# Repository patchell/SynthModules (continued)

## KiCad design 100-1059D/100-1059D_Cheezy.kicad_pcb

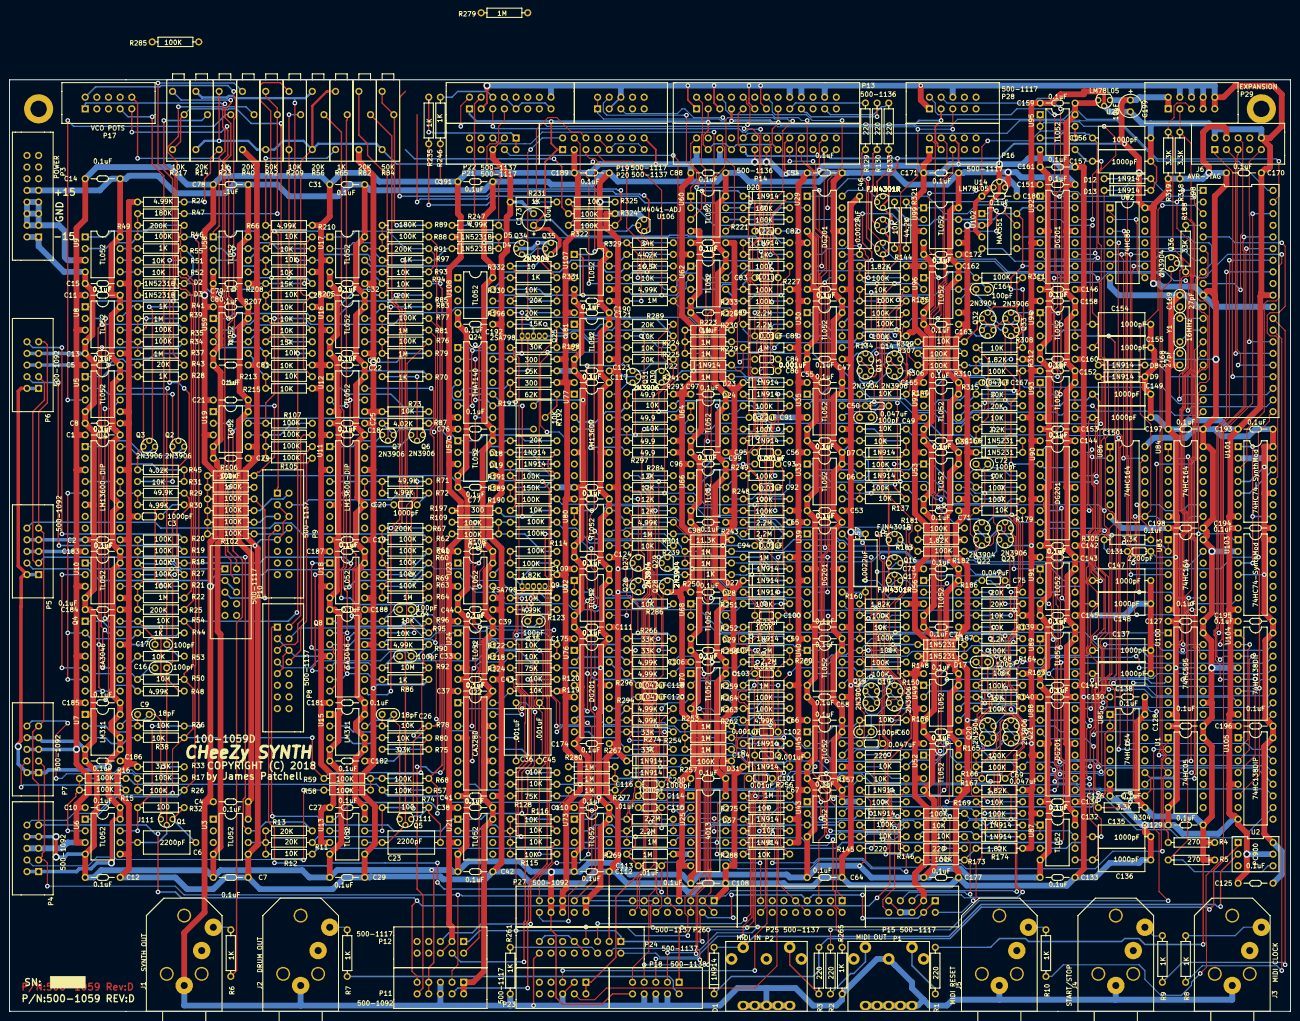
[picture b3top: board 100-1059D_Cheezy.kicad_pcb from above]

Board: 2 copper layers, 279.4 x 203.2 mm, 720 parts (0 on the bottom side), 505 nets.

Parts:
C1, C2, C4, C5, C7, C8, C10, C11, C12, C13, C14, C15, C18, C19, C21, C22, C24, C25, C27, C28, C29, C30, C31, C32, C37, C38, C39, C40, C41, C42, C43, C44, C47, C48, C51, C52, C53, C54, C55, C56, C58, C59, C62, C63, C64, C65, C66, C67, C70, C71, C73, C74, C76, C77, C87, C88, C89, C90, C96, C97, C98, C99, C105, C106, C107, C108, C109, C110, C111, C112, C117, C119, C121, C122, C123, C124, C125, C126, C127, C128, C129, C130, C132, C133, C134, C139, C140, C141, C142, C143, C144, C145, C146, C151, C152, C153, C158, C159, C160, C161, C162, C163, C165, C166, C170, C171, C172, C174, C175, C176, C177, C178, C179, C180, C181, C182, C183, C184, C185, C186, C187, C188, C189, C190, C191, C192, C193, C194, C195, C196, C197, C198, C200: 0.1uF; CAP-Bypass-0_3
C3, C20, C114, C116: 1000pF; CAP-GREENIE-0_2
C6, C23: 2200pF; CAP-AXIAL-0.5x0.2
C9, C26: 18pF; CAP-0.1
C16, C17, C33, C34, C35, C49, C60, C68, C72, C164: 100pF; CAP-0.1
C36, C45: .001uF; CAP-AXIAL-0.5x0.2
C46, C57: 0.0022uF; CAP-AXIAL-0.5x0.2
C50, C61, C69, C75, C118, C120, C167: 0.047uF; CAP-GREENIE-0_2
C78, C79, C80, C81: .1uF; CAP-Bypass-0_3
C82, C91, C100: 0.22uF; CAP-GREENIE-0_2
C83, C85, C92, C94, C101, C103: 0.01uF; CAP-GREENIE-0_2
C84, C86, C93, C95, C102, C104: 0.001uF; CAP-GREENIE-0_2
C113, C115: .01uF; CAP-GREENIE-0_2
C131: 2200pF; CAP-GREENIE-0_2
C135, C136, C137, C138, C147, C148, C149, C150, C154, C155, C156, C157: 1000pF; CAP-AXIAL-0.5x0.2
C168, C169: 27pF; CAP-0.1
C173, C199: 10uF; CapPol-Rad-0.2x0.1
D1, D6, D7, D8, D9, D10, D11, D12, D13, D14, D15, D18, D19, D20, D21, D22, D23, D24, D25, D26, D27, D28, D29, D30, D31, D32, D33, D35, D37: 1N914; DIODE0.4
D2, D3, D4, D5: 1N5231B; DIODE0.4
D16, D17, D38, D39: 1N5231; DIODE0.4
J1: SYNTH OUT; PHONE-SC112A
J2: DRUM OUT; PHONE-SC112A
J3: MIDI CLOCK; PHONE-SC112A
J4: START/STOP; PHONE-SC112A
J5: MIDI RESET; PHONE-SC112A
J6: AVR-JTAG; IDC5x2_Vert
P1: MIDI OUT; DIN-5-PIN
P2: MIDI IN; DIN-5-PIN
P3: POWER; IDC8x2_Vert
P4, P5, P6, P7, P11, P27: 500-1092; IDC5x2_Vert
P8, P9, P20, P22, P24, P25, P26: 500-1137; IDC8x2_Vert
P10, P12, P15, P16, P19, P21, P23, P28: 500-1117; IDC5x2_Vert
P13, P14: 500-1136; IDC13x2_Vert
P17: VCO POTS; IDC5x2_Vert
P18: 500-1138; IDC5x2_Vert
P29: EXPANSION; IDC5x2_Vert
P30, P31: PAD; MountingHole_140
Q1, Q5: J111; TO92
Q2, Q3, Q6, Q7, Q30, Q31: 2N3906; TO92
Q4, Q8: CA3046; DIP-14
Q9, Q25: 2SA798
Q10, Q11, Q12, Q15, Q16, Q17: FJN4301R; TO92
Q13, Q18, Q20, Q22, Q32: 2N3904; DUAL_TO92
Q14, Q19, Q21, Q23, Q33: 2N3906; DUAL_TO92
Q24: THAT140; DIP-14
Q26, Q27, Q28, Q29, Q34, Q35, Q36: 2N3904; TO92
R1, R2, R3, R129, R130, R133, R145, R146, R149: 220; AXIAL0_4
R4, R5: 270; AXIAL0_4
R6, R7, R8, R9, R10, R28, R41, R44, R55, R70, R83, R86, R97, R220, R231, R235, R246, R250, R261, R265, R331: 1K; AXIAL0_4
R11, R13, R43, R85, R184, R186, R196, R202, R289, R291, R313, R315, R333: 20K; AXIAL0_4
R12, R31, R36, R38, R51, R52, R53, R54, R73, R78, R80, R93, R94, R95, R96, R112, R113, R115, R116, R118, R119, R120, R122, R126, R127, R137, R139, R140, R141, R143, R153, R155, R156, R157, R159, R168, R169, R171, R175, R176, R179, R180, R185, R195, R203, R204, R205, R206, R207, R210, R211, R212, R213, R214, R215, R218, R219, R275, R286, R288, R290, R292, R299, R300, R302, R308, R309, R314, R320, R325, R327, R330: 10K; AXIAL0_4
R14, R40, R56, R82: 20K; Trimpot-3006
R15, R16, R17, R18, R19, R20, R21, R26, R27, R34, R35, R46, R57, R58, R59, R60, R61, R62, R63, R68, R69, R76, R77, R88, R98, R99, R100, R101, R102, R103, R104, R105, R106, R107, R108, R109, R110, R111, R114, R117, R131, R132, R134, R135, R136, R138, R142, R147, R148, R150, R151, R152, R154, R158, R161, R162, R163, R164, R165, R166, R170, R172, R173, R177, R178, R181, R182, R190, R191, R221, R222, R227, R233, R234, R236, R237, R242, R248, R249, R251, R252, R257, R263, R264, R285, R306, R307, R310, R311, R322, R324: 100K; AXIAL0_4
R22, R37, R39, R64, R79, R81, R223, R224, R225, R226, R229, R238, R239, R240, R241, R244, R253, R254, R255, R256, R259, R269, R273, R276, R277, R279, R280: 1M; AXIAL0_4
R23, R65: 1K; Trimpot-3006
R24, R30, R48, R66, R72, R90, R123, R232, R247, R262, R281, R282, R294, R296, R303: 4.99K; AXIAL0_4
R25, R49, R67, R91: 200K; AXIAL0_4
R29, R71: 49.9K; AXIAL0_4
R32, R74: 100; AXIAL0_4
R33, R75, R304, R305, R318, R319: 3.3K; AXIAL0_4
R42, R84: 50K; Trimpot-3006
R45, R87: 4.02K; AXIAL0_4
R47, R89: 180K; AXIAL0_4
R50, R92, R125: 10M; AXIAL0_4
R121, R144, R160, R167, R174, R183, R312: 1.82K; AXIAL0_4
R124, R128: 75K; AXIAL0_4
R187, R316: 2.2K; AXIAL0_4
R188, R266, R267, R274, R278: 33K; AXIAL0_4
R189: 150K; AXIAL0_4
R192: 10K; Trimpot
R193: 62K; AXIAL0_4
R194, R197, R201: 300; AXIAL0_4
R198: 30K; AXIAL0_4
R199, R200, R208, R216: 15K; AXIAL0_4
R209, R217: 10K; Trimpot-3006
R228, R230, R243, R245, R258, R260, R268, R272: 2.2M; AXIAL0_4
R270, R271, R283, R284: 12K; AXIAL0_4
R293, R295, R297, R298: 49.9; AXIAL0_4
R301: 11.3K; AXIAL0_4
R321, R328: 44.2K; AXIAL0_4
R326: 16.5K; AXIAL0_4
R329: 34K; AXIAL0_4
R332: 10; AXIAL0_4
U1: 74HC05; DIP-14
U2: PC900; DIP-6
U3, U5, U6, U8, U9, U10, U12, U13, U16, U17, U18, U19, U21, U23, U24, U30, U33, U35, U40, U43, U45, U49, U52, U53, U56, U57, U58, U59, U60, U62, U64, U66, U68, U70, U72, U73, U80, U81, U87, U89, U91, U93, U94, U95, U96, U97, U99, U107, U108: TL052; DIP8
U4, U11: LM13600-DIP; DIP-16
U7, U15: LM311; DIP8
U14, U20: LM78L05; TO92
U22: CA3280; DIP-16
U25: 4013; DIP-14
U29, U39, U76, U88, U90, U92: DG201; DIP-16
U77: LM13600; DIP-16
U82: 74HC86; DIP-14
U83, U84, U85, U86: 74HC164; DIP-14
U98: ATMEGA1284-dip; DIP-40
U100: 74HC595; DIP-16
U101, U103: 74HC74-SynthMod; DIP-14
U102: MAX551; DIP8
U104, U105: 74HC138DIP; DIP-16
U106: LM4041-ADJ; TO92
Y1: 16MHz; XTAL

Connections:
+10: C173.1, P12.1, P13.3, P13.7, P13.15, P14.3, P14.7, P14.15, P15.1, P15.4, P16.3, P20.1, P22.1, P24.1, P25.4, P25.7, P26.4, P28.3, Q35.1, R332.1, R333.2
+15V0: C1.1, C4.1, C5.1, C10.1, C11.1, C14.1, C18.1, C21.1, C22.1, C27.1, C28.1, C31.1, C37.1, C38.1, C39.1, C40.1, C48.1, C54.1, C55.1, C56.1, C59.1, C65.1, C66.1, C67.1, C70.1, C73.1, C76.1, C78.1, C80.1, C87.1, C88.1, C96.1, C97.1, C105.1, C106.1, C109.1, C110.1, C117.1, C121.1, C122.1, C132.1, C139.1, C140.1, C143.1, C144.1, C151.1, C152.1, C158.1, C159.1, C162.1, C165.1, C171.1, C175.1, C176.1, C178.1, C181.1, C183.1, C185.1, C187.1, C189.1, C191.1, C200.1, P3.9, P3.10, P4.1, P4.2, P5.1, P5.2, P6.1, P6.2, P7.1, P7.2, P11.1, P11.2, P18.1, P25.15, P26.11, P26.13, P26.15, P27.1, P27.2, Q34.3, R124.2, R128.2, R136.1, R141.1, R152.1, R157.1, R192.1, R198.1, R200.1, R203.1, R303.1, R325.1, U3.8, U4.11, U5.8, U6.8, U7.5, U7.6, U7.8, U8.8, U9.8, U10.8, U11.11, U12.8, U13.8, U14.3, U15.5, U15.6, U15.8, U16.8, U17.8, U18.8, U19.8, U20.3, U21.8, U22.11, U22.14, U23.8, U24.8, U25.5, U25.9, U25.14, U29.13, U30.8, U33.8, U35.8, U39.13, U40.8, U43.8, U45.8, U49.8, U52.8, U53.8, U56.8, U57.8, U58.8, U59.8, U60.8, U62.8, U64.8, U66.8, U68.8, U70.8, U72.8, U73.8, U76.13, U77.11, U80.8, U81.8, U87.8, U88.13, U89.8, U90.13, U91.8, U92.13, U93.8, U94.8, U95.8, U96.8, U97.8, U99.8, U107.8, U108.8
-10: R11.1, R125.1
-15V0: C2.1, C7.1, C8.1, C12.1, C13.1, C15.1, C19.1, C24.1, C25.1, C29.1, C30.1, C32.1, C41.1, C42.1, C43.1, C44.1, C47.1, C51.1, C52.1, C53.1, C58.1, C62.1, C63.1, C64.1, C71.1, C74.1, C77.1, C79.1, C81.1, C89.1, C90.1, C98.1, C99.1, C107.1, C108.1, C111.1, C112.1, C119.1, C123.1, C124.1, C133.1, C134.1, C141.1, C142.1, C145.1, C146.1, C153.1, C160.1, C161.1, C163.1, C166.1, C172.1, C174.1, C177.1, C179.1, C182.1, C184.1, C186.1, C188.1, C190.1, C192.1, P3.1, P3.2, P4.7, P4.8, P5.7, P5.8, P6.7, P6.8, P7.7, P7.8, P11.7, P11.8, P18.10, P27.7, P27.8, R138.2, R154.2, R189.2, R192.3, R199.2, U3.4, U4.6, U5.4, U6.4, U7.1, U7.4, U8.4, U9.4, U10.4, U11.6, U12.4, U13.4, U15.1, U15.4, U16.4, U17.4, U18.4, U19.4, U21.4, U22.4, U23.4, U24.4, U29.4, U30.4, U33.4, U35.4, U39.4, U40.4, U43.4, U45.4, U49.4, U52.4, U53.4, U56.4, U57.4, U58.4, U59.4, U60.4, U62.4, U64.4, U66.4, U68.4, U70.4, U72.4, U73.4, U76.4, U77.6, U80.4, U81.4, U87.4, U88.4, U89.4, U90.4, U91.4, U92.4, U93.4, U94.4, U95.4, U96.4, U97.4, U99.4, U107.4, U108.4
/+5Vref: P4.10, R14.1, R38.2, R50.1, R54.1, R56.1, R59.1, R80.2, R92.1, R96.1, R204.1, R212.1, R328.1, U107.7
/-5Vref: R14.3, R23.1, R42.3, R56.3, R65.1, R84.3, R205.1, R213.1, R327.2, R329.1, R330.1, U107.1
/CYMBAL: P25.5, R276.1, R280.1, U93.6, U93.7
/CYMBAL_LFO: P28.4, R306.2, U94.1, U94.2
/CYMBAL_TRG: R188.1, U98.4
/DRM1: R224.2, U91.1, U91.2
/DRM1_TRG: C83.1, D20.2, U98.19
/DRM2: R239.2, U91.6, U91.7
/DRM2_TRG: C92.1, D24.2, U98.20
/DRM3: R254.2, U93.1, U93.2
/DRM3_TRG: C101.1, D28.2, U98.21
/Drum Synth/CYMBAL/ATK2: P26.5, P26.6, R296.2
/Drum Synth/CYMBAL/ATTACK1: P25.8, P25.9, R282.2
/Drum Synth/CYMBAL/EG1: P27.3, R286.2, R291.1, U72.1, U72.2
/Drum Synth/CYMBAL/EG2: R289.1, R302.2, U80.1, U80.2
/Drum Synth/CYMBAL/LFO-A: P27.9, R299.2, U81.7
/Drum Synth/CYMBAL/OUT: P18.9, R300.2, U81.1
/Drum Synth/CYMBAL/REL1: P26.2, P26.3, R281.2
/Drum Synth/CYMBAL/REL2: P26.8, P26.9, R294.2
/Drum Synth/CYMBAL/RESONANCE: P25.2, R273.1
/Drum Synth/CYMBAL/SA0: R267.1, U25.13, U76.8
/Drum Synth/CYMBAL/SA1: R266.1, U25.12, U76.1
/Drum Synth/CYMBAL/SB0: R278.1, U25.1, U76.16
/Drum Synth/CYMBAL/SB1: R274.1, U25.2, U76.9
/Drum Synth/CYMBAL/TRIG: Q36.3, R203.2, U25.3, U25.11
/Drum Synth/DRUM1/OUT: P18.3, R234.1, U62.7
/Drum Synth/Drum2/OUT: P18.5, R249.1, U66.7
/Drum Synth/Drum3/OUT: P18.7, R264.1, U70.7
/Drum Synth/LFO: D38.1, R290.1, R308.1, R316.1
/Drum Synth/OUT: P18.2, R7.1
/FILT_PITCH: R110.1, U89.1, U89.2
/GLD_RATE_DN: R173.2, U95.6, U95.7
/GLD_RATE_UP: R166.2, U95.1, U95.2
/Midi/CLR_IRQ: U98.18, U103.1
/Midi/DAC: U29.10, U39.10, U88.2, U88.7, U88.10, U88.15, U90.2, U90.7, U90.10, U90.15, U92.2, U92.7, U92.10, U92.15, U99.7, U102.8
/Midi/DACDONE_IRQ: U98.16, U103.6
/Midi/DACSEL0: U98.36, U104.1, U105.1
/Midi/DACSEL1: U98.35, U104.2, U105.2
/Midi/DACSEL2: U98.34, U104.3, U105.3
/Midi/DACSEL3: U98.33, U104.5, U105.4
/Midi/DAC_CLK: U98.5, U101.11
/Midi/EG1_STATE_A: Q10.3, U29.1, U100.15
/Midi/EG1_STATE_B: Q11.3, U29.8, U100.1
/Midi/EG1_STATE_C: Q12.3, U29.16, U100.2
/Midi/EG2_STATE_A: Q15.3, U39.1, U100.3
/Midi/EG2_STATE_B: Q16.3, U39.8, U100.4
/Midi/EG2_STATE_C: Q17.3, U39.16, U100.5
/Midi/LD_DAC: U98.7, U101.3, U102.4
/Midi/LD_OUTPORT: U98.1, U100.12
/Midi/MIDI_CLOCK: R8.1, U98.28
/Midi/MIDI_IN: R5.2, U2.4, U98.14
/Midi/MIDI_OUT: U1.3, U98.15
/Midi/MIDI_RESET: R10.1, U98.38
/Midi/MOSI: U98.6, U100.14, U102.5
/Midi/SCL: P29.3, R318.2, U98.22
/Midi/SDA: P29.5, R319.2, U98.23
/Midi/SPICLK: U98.8, U100.11, U102.6
/Midi/START_STOP: R9.1, U98.29
/Midi/STB0: U88.1, U104.15
/Midi/STB1: U88.8, U104.14
/Midi/STB2: U88.16, U104.13
/Midi/STB3: U88.9, U104.12
/Midi/STB4: U90.1, U104.11
/Midi/STB5: U90.8, U104.10
/Midi/STB6: U90.16, U104.9
/Midi/STB7: U90.9, U104.7
/Midi/STB8: U92.1, U105.15
/Midi/STB9: U92.8, U105.14
/Midi/STB10: U92.16, U105.13
/Midi/STB11: U92.9, U105.12
/Midi/TCK: J6.1, U98.24
/Midi/TDI: J6.9, U98.27
/Midi/TDO: J6.3, U98.26
/Midi/TMS: J6.5, U98.25
/NOISE: C113.1, C131.1, P9.7, R305.2
/NOISE_CLOCK: U83.8, U84.8, U85.8, U86.8, U98.2
/PITCH: R162.2, U87.1, U87.2
/PITCH_BEND: R12.1, U89.6, U89.7
/PULSEWIDTH: R16.1, R57.1, U94.6, U94.7
/References/DACREF: R320.1, R322.1, R325.2, R326.2, U106.2
/Synth/ADSR: C50.2, P4.3, P7.3, P11.3, P16.4, R131.1, R177.2, U35.7
/Synth/EG1_READY: D8.2, D9.1, R143.1, U98.17
/Synth/EG1_SUS_V: P13.10, U98.39
/Synth/EG2_READY: D12.2, D13.1, R159.1, U98.3
/Synth/EG2_SUS_V: P14.10, U98.40
/Synth/Envelope1/ATTACK: P13.2, U29.2
/Synth/Envelope1/DECAY: P13.6, U29.7
/Synth/Envelope1/RELEASE: P13.14, U29.15
/Synth/Envelope1/TIMECONST: R142.2, U29.3, U29.6, U29.14
/Synth/Envelope2/ATTACK: P14.2, U39.2
/Synth/Envelope2/DECAY: P14.6, U39.7
/Synth/Envelope2/RELEASE: P14.14, U39.15
/Synth/Envelope2/TIMECONST: R158.2, U39.3, U39.6, U39.14
/Synth/Filter/BP: C36.2, P8.4, P12.4, R127.1, U24.1
/Synth/Filter/FC1: P12.2, R109.1
/Synth/Filter/FC2: P11.4, R111.1
/Synth/Filter/FC3: P11.10, R108.1
/Synth/Filter/IN: R106.2, R112.1, U19.1
/Synth/Filter/Q: P12.5, R113.1
/Synth/GLIDE/OUT: C69.2, R18.1, R60.1, R161.2, U52.7
/Synth/GLIDE/RAMP_DOWN_POT: P15.2, R172.2
/Synth/GLIDE/RAMP_UP_POT: P15.5, R165.2
/Synth/LFO: D16.1, P4.9, P5.9, P6.9, P7.9, P11.9, R179.1, R187.1
/Synth/Mixer/FIN1: P8.1, R116.2, R120.1, U21.1
/Synth/Mixer/FIN3: C45.2, P8.7, R115.2, U24.7
/Synth/Mixer/FOUT: R107.2, R196.2, U19.7
/Synth/Mixer/IN1: P10.1, R49.2, R51.2, U9.1
/Synth/Mixer/IN2: D2.1, P10.4, R55.1
/Synth/Mixer/IN3: P9.1, R91.2, R93.2, U17.1
/Synth/Mixer/IN4: D4.1, P9.4, R97.1
/Synth/OUT: R6.1, R202.1, U57.1
/Synth/PITCH POTS/POT1: P17.7, R21.1
/Synth/PITCH POTS/POT2: P17.3, R285.1
/Synth/PITCH POTS/minus1: P17.10, R219.2, U59.7
/Synth/PITCH POTS/minus2: P17.2, R211.2, U58.7
/Synth/PITCH POTS/plus1: P17.9, R218.2, U59.1
/Synth/PITCH POTS/plus2: P17.1, R210.2, U58.1
/Synth/PITCHBEND: P5.3, P6.3, R13.2, U3.7
/Synth/STB0: U29.9, U105.11
/Synth/STB1: U39.9, U105.10
/Synth/VCA/CV: C61.2, R147.1, R190.2, U45.7
/Synth/VCO1/PWM1: P7.4, R15.1
/Synth/VCO1/PWM3: P7.10, R17.1
/Synth/VCO1/TRACKING: R25.2, R40.2
/Synth/VCO1/VCO2: P6.4, R19.1
/Synth/VCO1/VCO3: P6.10, R20.1
/Synth/VCO2/PWM2: P4.4, R58.1
/Synth/VCO2/TRACKING: R67.2, R82.2
/Synth/VCO2/VCO2: P5.4, R61.1
/Synth/VCO2/VCO3: P5.10, R62.1
/VCO2_OFFSET: R63.1, U87.6, U87.7
GND: C1.2, C2.2, C3.2, C4.2, C5.2, C7.2, C8.2, C10.2, C11.2, C12.2, C13.2, C14.2, C15.2, C18.2, C19.2, C20.2, C21.2, C22.2, C24.2, C25.2, C27.2, C28.2, C29.2, C30.2, C31.2, C32.2, C37.2, C38.2, C39.2, C40.2, C41.2, C42.2, C43.2, C44.2, C46.2, C47.2, C48.2, C51.2, C52.2, C53.2, C54.2, C55.2, C56.2, C57.2, C58.2, C59.2, C62.2, C63.2, C64.2, C65.2, C66.2, C67.2, C70.2, C71.2, C73.2, C74.2, C76.2, C77.2, C78.2, C79.2, C80.2, C81.2, C82.2, C85.2, C87.2, C88.2, C89.2, C90.2, C91.2, C94.2, C96.2, C97.2, C98.2, C99.2, C100.2, C103.2, C105.2, C106.2, C107.2, C108.2, C109.2, C110.2, C111.2, C112.2, C115.2, C117.2, C118.2, C119.2, C120.2, C121.2, C122.2, C123.2, C124.2, C125.2, C126.2, C127.2, C128.2, C129.2, C130.2, C131.2, C132.2, C133.2, C134.2, C135.2, C136.2, C137.2, C138.2, C139.2, C140.2, C141.2, C142.2, C143.2, C144.2, C145.2, C146.2, C147.2, C148.2, C149.2, C150.2, C151.2, C152.2, C153.2, C154.2, C155.2, C156.2, C157.2, C158.2, C159.2, C160.2, C161.2, C162.2, C163.2, C165.2, C166.2, C168.2, C169.2, C170.2, C171.2, C172.2, C173.2, C174.2, C175.2, C176.2, C177.2, C178.2, C179.2, C180.2, C181.2, C182.2, C183.2, C184.2, C185.2, C186.2, C187.2, C188.2, C189.2, C190.2, C191.2, C192.2, C193.2, C194.2, C195.2, C196.2, C197.2, C198.2, C199.2, C200.2, D3.1, D5.1, D9.2, D13.2, D17.1, D23.1, D27.1, D31.1, D33.1, D35.2, D37.2, D39.1, J1.1, J2.1, J3.1, J4.1, J5.1, J6.2, J6.10, P1.2, P1.6, P1.7, P1.8, P1.9, P1.10, P2.6, P2.7, P2.8, P2.9, P2.10, P3.3, P3.4, P3.5, P3.6, P3.7, P3.8, P4.5, P4.6, P5.5, P5.6, P6.5, P6.6, P7.5, P7.6, P8.3, P8.6, P8.9, P9.3, P9.6, P9.9, P10.3, P10.6, P11.5, P11.6, P12.3, P12.6, P13.1, P13.5, P13.11, P13.13, P13.18, P13.20, P13.24, P14.1, P14.5, P14.11, P14.13, P14.18, P14.20, P14.24, P15.3, P15.6, P15.8, P15.9, P16.1, P16.6, P18.4, P18.6, P18.8, P19.3, P19.6, P20.3, P20.16, P21.3, P21.6, P22.3, P22.16, P23.3, P23.6, P24.3, P24.16, P25.6, P26.1, P26.7, P27.5, P27.6, P28.1, P28.6, P29.4, P29.6, P29.7, P29.8, P29.9, P29.10, Q4.4, Q4.12, Q8.4, Q8.12, Q9.5, Q13.5, Q14.2, Q18.5, Q19.2, Q20.5, Q21.2, Q22.5, Q23.2, Q24.7, Q25.4, Q25.5, Q26.1, Q27.1, Q28.1, Q29.1, Q30.2, Q31.2, Q32.5, Q33.2, Q36.1, R24.2, R31.2, R33.2, R37.2, R40.3, R44.2, R45.2, R66.2, R73.2, R75.2, R79.2, R82.3, R86.2, R87.2, R119.1, R121.2, R126.1, R134.2, R144.2, R150.2, R160.2, R163.1, R167.2, R174.2, R183.2, R185.2, R194.2, R197.2, R201.2, R206.2, R207.2, R214.2, R215.2, R227.2, R229.2, R231.2, R242.2, R244.2, R246.2, R257.2, R259.2, R261.2, R265.2, R269.2, R293.2, R295.2, R297.2, R298.2, R301.2, R312.2, R314.2, R324.2, U1.7, U2.5, U3.5, U4.3, U4.14, U5.5, U6.3, U6.5, U8.3, U9.3, U10.3, U10.5, U11.3, U11.14, U12.5, U13.3, U13.5, U14.2, U16.3, U17.3, U18.3, U18.5, U19.3, U19.5, U20.2, U21.3, U23.3, U23.5, U24.3, U24.5, U25.6, U25.7, U25.8, U29.5, U35.3, U35.5, U39.5, U45.3, U45.5, U49.3, U52.3, U52.5, U53.5, U56.3, U57.3, U57.5, U62.5, U66.5, U70.5, U76.5, U81.3, U81.5, U82.7, U83.7, U84.7, U85.7, U86.7, U88.5, U90.5, U92.5, U96.5, U97.3, U98.11, U98.31, U99.3, U99.5, U100.8, U100.13, U101.7, U102.2, U103.7, U104.8, U105.5, U105.8, U106.3, U107.3, U107.5, U108.3, U108.5
unnamed: C3.1, R30.2
unnamed: C6.1, Q1.2, Q4.1, U6.6
unnamed: C6.2, Q1.1, R32.1
unnamed: C9.1, R36.2, U7.2
unnamed: C9.2, Q1.3, R33.1, U7.7
unnamed: C16.1, Q4.5, R50.2, U10.2
unnamed: C16.2, R48.2, U10.1
unnamed: C17.1, Q4.14, R54.2, U5.6
unnamed: C17.2, R53.2, U5.7
unnamed: C20.1, R72.2
unnamed: C23.1, Q5.2, Q8.1, U13.6
unnamed: C23.2, Q5.1, R74.1
unnamed: C26.1, R78.2, U15.2
unnamed: C26.2, Q5.3, R75.1, U15.7
unnamed: C33.1, Q8.5, R92.2, U18.2
unnamed: C33.2, R90.2, U18.1
unnamed: C34.1, Q8.14, R96.2, U12.6
unnamed: C34.2, R95.2, U12.7
unnamed: C35.1, Q9.4, R125.2, U23.2
unnamed: C35.2, R123.2, U23.1
unnamed: C36.1, U22.13, U24.2
unnamed: C45.1, U22.12, U24.6
unnamed: C46.1, U29.11, U30.5
unnamed: C49.1, R140.2, U35.1
unnamed: C49.2, Q13.3, Q14.3, R139.2, U35.2
unnamed: C50.1, Q13.6, Q14.6, U35.6
unnamed: C57.1, U39.11, U40.5
unnamed: C60.1, R156.2, U45.1
unnamed: C60.2, Q18.3, Q19.3, R155.2, U45.2
unnamed: C61.1, Q18.6, Q19.6, U45.6
unnamed: C68.1, R171.2, U49.1
unnamed: C68.2, Q20.3, Q21.3, R168.2, U49.2
unnamed: C69.1, Q20.6, Q21.6, U52.6
unnamed: C72.1, R180.2, U53.7
unnamed: C72.2, Q22.3, Q23.3, R179.2, U53.6
unnamed: C75.1, Q22.6, Q23.6, U56.2
unnamed: C75.2, R184.2, U56.1
unnamed: C82.1, D20.1, D21.2, U60.3
unnamed: C83.2, R227.1, U62.3
unnamed: C84.1, R226.1, R228.1, U62.2
unnamed: C84.2, C86.1, D22.2, R223.1, R224.1, R225.1, R229.1
unnamed: C85.1, R228.2, R230.1
unnamed: C86.2, P20.4, R230.2, R232.2, U62.1
unnamed: C91.1, D24.1, D25.2, U64.3
unnamed: C92.2, R242.1, U66.3
unnamed: C93.1, R241.1, R243.1, U66.2
unnamed: C93.2, C95.1, D26.2, R238.1, R239.1, R240.1, R244.1
unnamed: C94.1, R243.2, R245.1
unnamed: C95.2, P22.4, R245.2, R247.2, U66.1
unnamed: C100.1, D28.1, D29.2, U68.3
unnamed: C101.2, R257.1, U70.3
unnamed: C102.1, R256.1, R258.1, U70.2
unnamed: C102.2, C104.1, D30.2, R253.1, R254.1, R255.1, R259.1
unnamed: C103.1, R258.2, R260.1
unnamed: C104.2, P24.4, R260.2, R262.2, U70.1
unnamed: C113.2, R269.1, U73.3
unnamed: C114.1, R268.1, R273.2, U73.2
unnamed: C114.2, C116.1, D32.2, R276.2, R277.2, R279.2, R280.2
unnamed: C115.1, R268.2, R272.1
unnamed: C116.2, P25.1, R272.2, R292.1, U73.1
unnamed: C118.1, U72.3, U76.3, U76.6
unnamed: C120.1, U76.11, U76.14, U80.3
unnamed: C126.1, R304.2, U83.9, U84.9, U85.9, U86.9
unnamed: C135.1, U87.3, U88.3
unnamed: C136.1, U87.5, U88.6
unnamed: C137.1, U88.14, U89.3
unnamed: C138.1, U88.11, U89.5
unnamed: C147.1, U90.3, U91.3
unnamed: C148.1, U90.6, U91.5
unnamed: C149.1, U90.14, U93.3
unnamed: C150.1, U90.11, U93.5
unnamed: C154.1, U92.3, U94.3
unnamed: C155.1, U92.6, U94.5
unnamed: C156.1, U92.14, U95.3
unnamed: C157.1, U92.11, U95.5
unnamed: C164.1, R309.2, U96.7
unnamed: C164.2, Q32.3, Q33.3, R308.2, U96.6
unnamed: C167.1, Q32.6, Q33.6, U97.2
unnamed: C167.2, R313.2, U97.1
unnamed: C168.1, U98.13, Y1.1
unnamed: C169.1, U98.12, Y1.2
unnamed: C180.1, U14.1, U102.3
unnamed: D1.1, R3.2, U2.1
unnamed: D1.2, P2.5, U2.2
unnamed: D2.2, D3.2
unnamed: D4.2, D5.2
unnamed: D6.1, U33.1
unnamed: D6.2, D7.2, R141.2, R143.2
unnamed: D7.1, U33.7
unnamed: D10.1, U43.1
unnamed: D10.2, D11.2, R157.2, R159.2
unnamed: D11.1, U43.7
unnamed: D14.1, D15.2, R170.1, U52.1
unnamed: D14.2, R176.2
unnamed: D15.1, R175.2
unnamed: D16.2, D17.2
unnamed: D18.1, D19.2, U57.7
unnamed: D18.2, R189.1, R190.1, R191.2, U57.6
unnamed: D19.1, R191.1, R195.2
unnamed: D21.1, R220.1
unnamed: D22.1, D23.2
unnamed: D25.1, R235.1
unnamed: D26.1, D27.2
unnamed: D29.1, R250.1
unnamed: D30.1, D31.2
unnamed: D32.1, D33.2
unnamed: D35.1, R275.1, U25.10
unnamed: D37.1, R288.1, U25.4
unnamed: D38.2, D39.2
unnamed: J1.3, R6.2
unnamed: J2.3, R7.2
unnamed: J3.3, R8.2
unnamed: J4.3, R9.2
unnamed: J5.3, R10.2
unnamed: J6.6, U98.9
unnamed: P1.4, R1.1
unnamed: P1.5, R2.1
unnamed: P2.4, R3.1
unnamed: P8.2, R103.1
unnamed: P8.5, R104.1
unnamed: P8.8, R105.1
unnamed: P9.2, R100.1
unnamed: P9.5, R101.1
unnamed: P9.8, R102.1
unnamed: P10.2, R98.1
unnamed: P10.5, R99.1
unnamed: P13.17, R129.2
unnamed: P13.19, R130.2
unnamed: P13.23, R133.2
unnamed: P14.17, R145.2
unnamed: P14.19, R146.2
unnamed: P14.23, R149.2
unnamed: P15.7, R175.1
unnamed: P15.10, R176.1
unnamed: P16.2, R181.2
unnamed: P16.5, U53.3
unnamed: P19.1, P19.2, R220.2
unnamed: P19.4, R221.2, U60.1, U60.2
unnamed: P19.5, U60.5
unnamed: P20.2, R223.2
unnamed: P20.5, R226.2
unnamed: P20.6, R231.1
unnamed: P20.7, R232.1, R233.2
unnamed: P20.8, P20.9, P20.15
unnamed: P21.1, P21.2, R235.2
unnamed: P21.4, R236.2, U64.1, U64.2
unnamed: P21.5, U64.5
unnamed: P22.2, R238.2
unnamed: P22.5, R241.2
unnamed: P22.6, R246.1
unnamed: P22.7, R247.1, R248.2
unnamed: P22.8, P22.9, P22.15
unnamed: P23.1, P23.2, R250.2
unnamed: P23.4, R251.2, U68.1, U68.2
unnamed: P23.5, U68.5
unnamed: P24.2, R253.2
unnamed: P24.5, R256.2
unnamed: P24.6, R261.1
unnamed: P24.7, R262.1, R263.2
unnamed: P24.8, P24.9, P24.15
unnamed: P25.3, R265.1
unnamed: P25.16, R271.2
unnamed: P26.12, R270.2
unnamed: P26.14, R284.2
unnamed: P26.16, R283.2
unnamed: P27.4, R279.1
unnamed: P27.10, R277.1
unnamed: P28.2, R310.2
unnamed: P28.5, U96.3
unnamed: Q2.1, R31.1, U5.2
unnamed: Q2.2, R28.1
unnamed: Q2.3, U4.16
unnamed: Q3.1, R39.2, R45.1
unnamed: Q3.2, R41.1
unnamed: Q3.3, U4.1
unnamed: Q4.2, Q4.6, R44.1, U4.5
unnamed: Q4.3, Q4.7, R35.1, R48.1
unnamed: Q4.8, R43.2, U8.2
unnamed: Q4.10, Q4.13, R34.1, R53.1
unnamed: Q6.1, R73.1, U12.2
unnamed: Q6.2, R70.1
unnamed: Q6.3, U11.16
unnamed: Q7.1, R81.2, R87.1
unnamed: Q7.2, R83.1
unnamed: Q7.3, U11.1
unnamed: Q8.2, Q8.6, R86.1, U11.5
unnamed: Q8.3, Q8.7, R77.1, R90.1
unnamed: Q8.8, R85.2, U16.2
unnamed: Q8.10, Q8.13, R76.1, R95.1
unnamed: Q9.1, R117.2, R121.1
unnamed: Q9.2, R118.2, R122.2
unnamed: Q9.3, R123.1
unnamed: Q10.2, R129.1
unnamed: Q11.2, R130.1
unnamed: Q12.2, R133.1
unnamed: Q13.1, Q13.4, Q14.1, Q14.4, R140.1
unnamed: Q13.2, Q14.5, R142.1, R144.1
unnamed: Q15.2, R145.1
unnamed: Q16.2, R146.1
unnamed: Q17.2, R149.1
unnamed: Q18.1, Q18.4, Q19.1, Q19.4, R156.1
unnamed: Q18.2, Q19.5, R158.1, R160.1
unnamed: Q20.1, Q20.4, Q21.1, Q21.4, R171.1
unnamed: Q20.2, R165.1, R166.1, R167.1
unnamed: Q21.5, R172.1, R173.1, R174.1
unnamed: Q22.1, Q22.4, Q23.1, Q23.4, R180.1
unnamed: Q22.2, Q23.5, R181.1, R182.1, R183.1
unnamed: Q24.1, Q24.6, Q25.1, R196.1
unnamed: Q24.2, Q24.9, R195.1, R197.1
unnamed: Q24.5, R193.1, R194.1
unnamed: Q24.4, Q24.10, R198.2
unnamed: Q24.3, Q24.12, Q25.2, R199.1
unnamed: Q24.13, R201.1
unnamed: Q24.8, Q24.14, R202.2, U57.2
unnamed: Q25.3, R200.2
unnamed: Q26.2, R266.2
unnamed: Q26.3, R270.1
unnamed: Q27.2, R267.2
unnamed: Q27.3, R271.1
unnamed: Q28.2, R274.2
unnamed: Q28.3, R283.1
unnamed: Q29.2, R278.2
unnamed: Q29.3, R284.1
unnamed: Q30.1, R289.2
unnamed: Q31.1, R291.2
unnamed: Q31.3, U77.16
unnamed: Q32.1, Q32.4, Q33.1, Q33.4, R309.1
unnamed: Q32.2, Q33.5, R310.1, R311.1, R312.1
unnamed: Q34.1, Q35.2, R332.2
unnamed: Q34.2, Q35.3, R331.1
unnamed: Q36.2, R188.2
unnamed: R2.2, U1.2
unnamed: R4.2, U1.1, U1.4
unnamed: R11.2, R12.2, R13.1, U3.6
unnamed: R14.2, R22.1
unnamed: R15.2, R16.2, R17.2, R26.1, U6.2
unnamed: R18.2, R19.2, R20.2, R21.2, R22.2, R25.1, R27.1, U10.6
unnamed: R23.2, U5.3
unnamed: R23.3, R24.1
unnamed: R26.2, R52.2, U6.1
unnamed: R27.2, R29.1, U10.7
unnamed: R28.2, U5.1
unnamed: R29.2, R30.1, U4.4, U4.12, U4.13
unnamed: R32.2, R36.1, R46.1, U6.7
unnamed: R34.2, R37.1, U8.5
unnamed: R35.2, R39.1, U8.6
unnamed: R38.1, U7.3
unnamed: R40.1, R43.1, U8.1
unnamed: R41.2, U8.7
unnamed: R42.1, R42.2, R47.1
unnamed: R46.2, R47.2, R49.1, U9.2
unnamed: R51.1, U9.6
unnamed: R52.1, U9.5
unnamed: R55.2, U9.7
unnamed: R56.2, R64.1
unnamed: R57.2, R58.2, R59.2, R68.1, U13.2
unnamed: R65.2, U12.3
unnamed: R65.3, R66.1
unnamed: R68.2, R94.2, U13.1
unnamed: R69.2, R71.1, U18.7
unnamed: R70.2, U12.1
unnamed: R71.2, R72.1, U11.4, U11.12, U11.13
unnamed: R74.2, R78.1, R88.1, U13.7
unnamed: R76.2, R79.1, U16.5
unnamed: R77.2, R81.1, U16.6
unnamed: R80.1, U15.3
unnamed: R82.1, R85.1, U16.1
unnamed: R83.2, U16.7
unnamed: R84.1, R84.2, R89.1
unnamed: R88.2, R89.2, R91.1, U17.2
unnamed: R93.1, U17.6
unnamed: R94.1, U17.5
unnamed: R97.2, U17.7
unnamed: R98.2, R99.2, R100.2, R101.2, R102.2, R106.1, U19.2
unnamed: R103.2, R104.2, R105.2, R107.1, U19.6
unnamed: R108.2, R109.2, R110.2, R111.2, R114.1, U23.6
unnamed: R112.2, R113.2, R115.1, R116.1, U21.2
unnamed: R114.2, R117.1, U23.7
unnamed: R118.1, U22.3
unnamed: R119.2, U22.16
unnamed: R120.2, U22.15
unnamed: R122.1, U22.6
unnamed: R124.1, U22.1
unnamed: R126.2, U22.9
unnamed: R127.2, U22.10
unnamed: R128.1, U22.8
unnamed: R131.2, R135.1, U30.2
unnamed: R132.1, U30.6, U30.7
unnamed: R132.2, R134.1, U30.3
unnamed: R135.2, R139.1, U30.1, U33.3, U33.6
unnamed: R136.2, R137.1, U33.2
unnamed: R137.2, R138.1, U33.5
unnamed: R147.2, R151.1, U40.2
unnamed: R148.1, U40.6, U40.7
unnamed: R148.2, R150.1, U40.3
unnamed: R151.2, R155.1, U40.1, U43.3, U43.6
unnamed: R152.2, R153.1, U43.2
unnamed: R153.2, R154.1, U43.5
unnamed: R161.1, R164.2, U49.6
unnamed: R162.1, R163.2, U49.5
unnamed: R164.1, R168.1, R169.2, U49.7
unnamed: R169.1, R170.2, U52.2
unnamed: R177.1, R178.2, U53.2
unnamed: R178.1, R182.2, U53.1
unnamed: R184.1, U56.6
unnamed: R185.1, R186.2, U56.5
unnamed: R186.1, R187.2, U56.7
unnamed: R192.2, R193.2
unnamed: R204.2, R206.1, U58.3
unnamed: R205.2, R207.1, U58.5
unnamed: R208.1, R210.1, U58.2
unnamed: R208.2, R209.2, R209.3
unnamed: R209.1, R211.1, U58.6
unnamed: R212.2, R214.1, U59.3
unnamed: R213.2, R215.1, U59.5
unnamed: R216.1, R218.1, U59.2
unnamed: R216.2, R217.2, R217.3
unnamed: R217.1, R219.1, U59.6
unnamed: R221.1, R222.2, U60.6
unnamed: R222.1, R225.2, U60.7
unnamed: R233.1, R234.2, U62.6
unnamed: R236.1, R237.2, U64.6
unnamed: R237.1, R240.2, U64.7
unnamed: R248.1, R249.2, U66.6
unnamed: R251.1, R252.2, U68.6
unnamed: R252.1, R255.2, U68.7
unnamed: R263.1, R264.2, U70.6
unnamed: R275.2, U72.7
unnamed: R281.1, U76.2
unnamed: R282.1, U76.7
unnamed: R60.2, R61.2, R62.2, R63.2, R64.2, R67.1, R69.1, R285.2, U18.6
unnamed: R286.1, U72.5
unnamed: R288.2, U80.7
unnamed: R290.2, R293.1, U77.4
unnamed: R292.2, R295.1, U77.13
unnamed: R294.1, U76.10
unnamed: R296.1, U76.15
unnamed: R297.1, U77.3
unnamed: R298.1, U77.14
unnamed: R299.1, U77.5, U81.6
unnamed: R300.1, U77.12, U81.2
unnamed: R301.1, R303.2, U72.6, U80.6
unnamed: R302.1, U80.5
unnamed: R305.1, U82.5, U86.13
unnamed: R306.1, R307.2, U96.2
unnamed: R307.1, R311.2, U96.1
unnamed: R313.1, U97.6
unnamed: R314.1, R315.2, U97.5
unnamed: R315.1, R316.2, U97.7
unnamed: R320.2, R321.1, U99.2
unnamed: R321.2, U99.1, U102.7
unnamed: R326.1, R329.2, U107.2
unnamed: R327.1, R328.2, U107.6
unnamed: R330.2, R333.1, U108.6
unnamed: R331.2, U108.7
unnamed: U82.1, U82.6
unnamed: U82.2, U82.8
unnamed: U82.3, U83.1, U83.2
unnamed: U82.4, U85.11
unnamed: U82.9, U83.3
unnamed: U82.10, U83.4
unnamed: U83.13, U84.1, U84.2
unnamed: U84.13, U85.1, U85.2
unnamed: U85.13, U86.1, U86.2
unnamed: U101.1, U101.8, U103.3, U104.6, U105.6
unnamed: U101.5, U101.12
unnamed: U99.6, U102.1
unnamed: U108.1, U108.2
VCC: C125.1, C127.1, C128.1, C129.1, C130.1, C170.1, C193.1, C194.1, C195.1, C196.1, C197.1, C198.1, C199.1, D8.1, D12.1, J6.4, P13.9, P14.9, P29.1, P29.2, Q10.1, Q11.1, Q12.1, Q15.1, Q16.1, Q17.1, R1.2, R4.1, R5.1, R304.1, R318.1, R319.1, U1.14, U2.6, U20.1, U82.14, U83.14, U84.14, U85.14, U86.14, U98.10, U98.30, U100.10, U100.16, U101.2, U101.4, U101.10, U101.13, U101.14, U103.2, U103.4, U103.14, U104.4, U104.16, U105.16

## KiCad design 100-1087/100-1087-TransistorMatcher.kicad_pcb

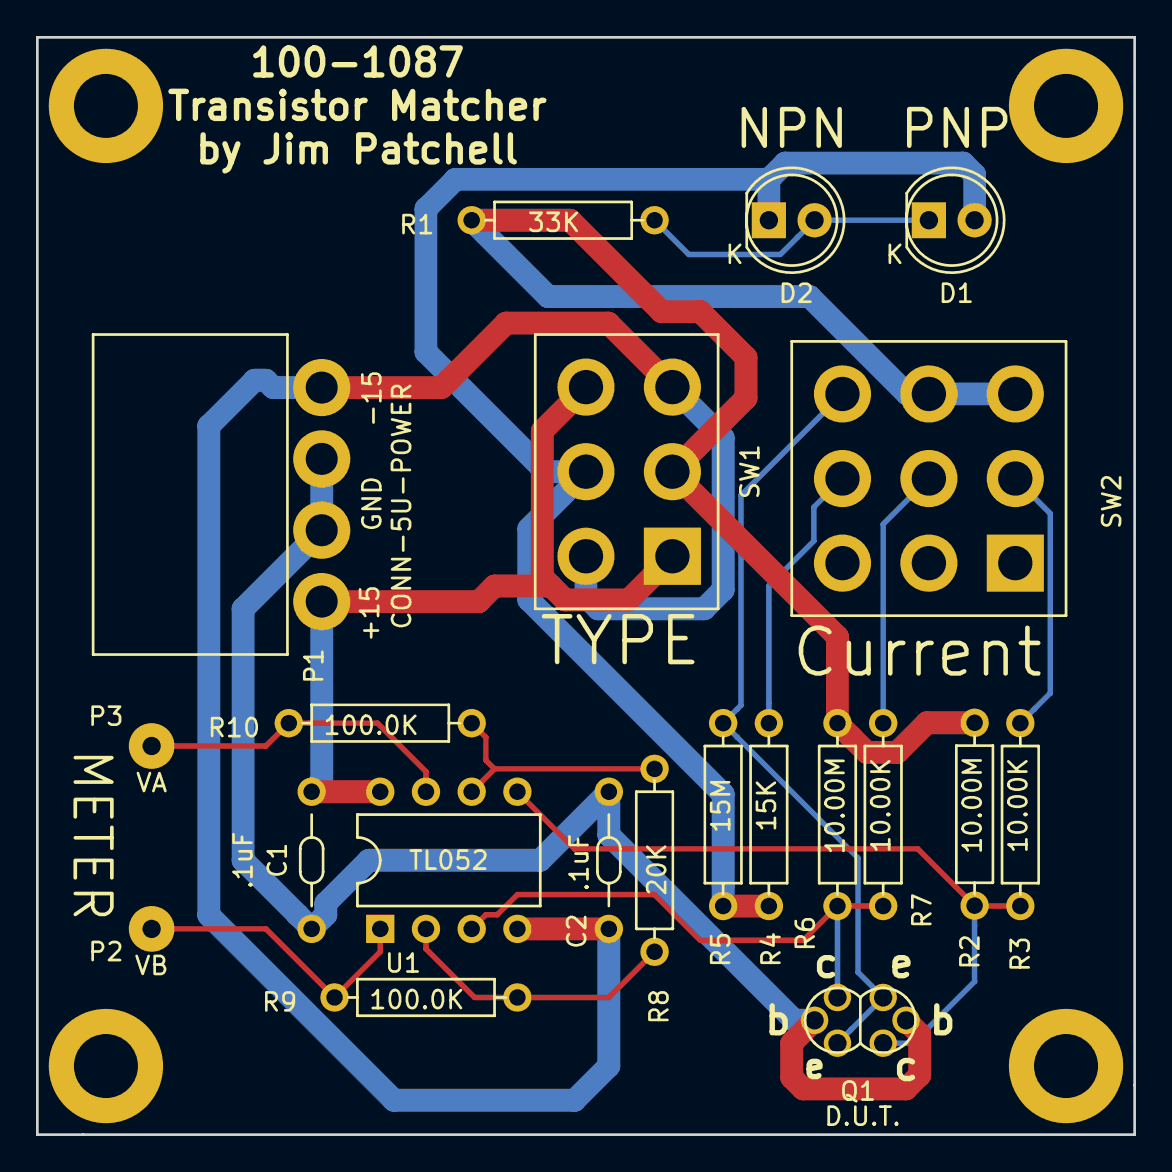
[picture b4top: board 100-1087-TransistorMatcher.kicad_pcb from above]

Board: 2 copper layers, 61.0 x 61.0 mm, 21 parts (0 on the bottom side), 16 nets.

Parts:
C1, C2: .1uF; CAP-Bypass-0.3
D1: PNP; LED-5MM
D2: NPN; LED-5MM
P1: CONN-5U-POWER; CONN-5U-POWER-RA
P2: VB; PAD
P3: VA; PAD
Q1: D.U.T.; DUAL_TO92
R1: 33K; AXIAL0.4
R2, R6: 10.00M; AXIAL0.4
R3, R7: 10.00K; AXIAL0.4
R4: 15K; AXIAL0.4
R5: 15M; AXIAL0.4
R8: 20K; AXIAL0.4
R9, R10: 100.0K; AXIAL0.4
SW1: TYPE; SW-NKK-DPDT
SW2: Current; SW-NKK-DP3T
U1: TL052; DIP8.3

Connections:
+15V0: C1.1, P1.1, SW1.1, SW1.6, U1.8
-15V0: C2.1, P1.4, SW1.3, SW1.4, U1.4
/VCC: R1.1, R2.1, R6.1, SW1.2, SW2.3, SW2.6
/VEE: D1.2, D2.1, R4.2, R5.2, SW1.5
GND: C1.2, C2.2, P1.2, P1.3, Q1.2, Q1.5
unnamed: D1.1, D2.2, R1.2
unnamed: P2.1, R9.1, U1.1
unnamed: P3.1, R10.1, U1.7
unnamed: Q1.1, Q1.4, R5.1, SW2.9
unnamed: Q1.3, R2.2, R3.2, U1.5
unnamed: Q1.6, R6.2, R7.2, U1.3
unnamed: R3.1, SW2.2
unnamed: R4.1, SW2.8
unnamed: R7.1, SW2.5
unnamed: R8.1, R9.2, U1.2
unnamed: R8.2, R10.2, U1.6

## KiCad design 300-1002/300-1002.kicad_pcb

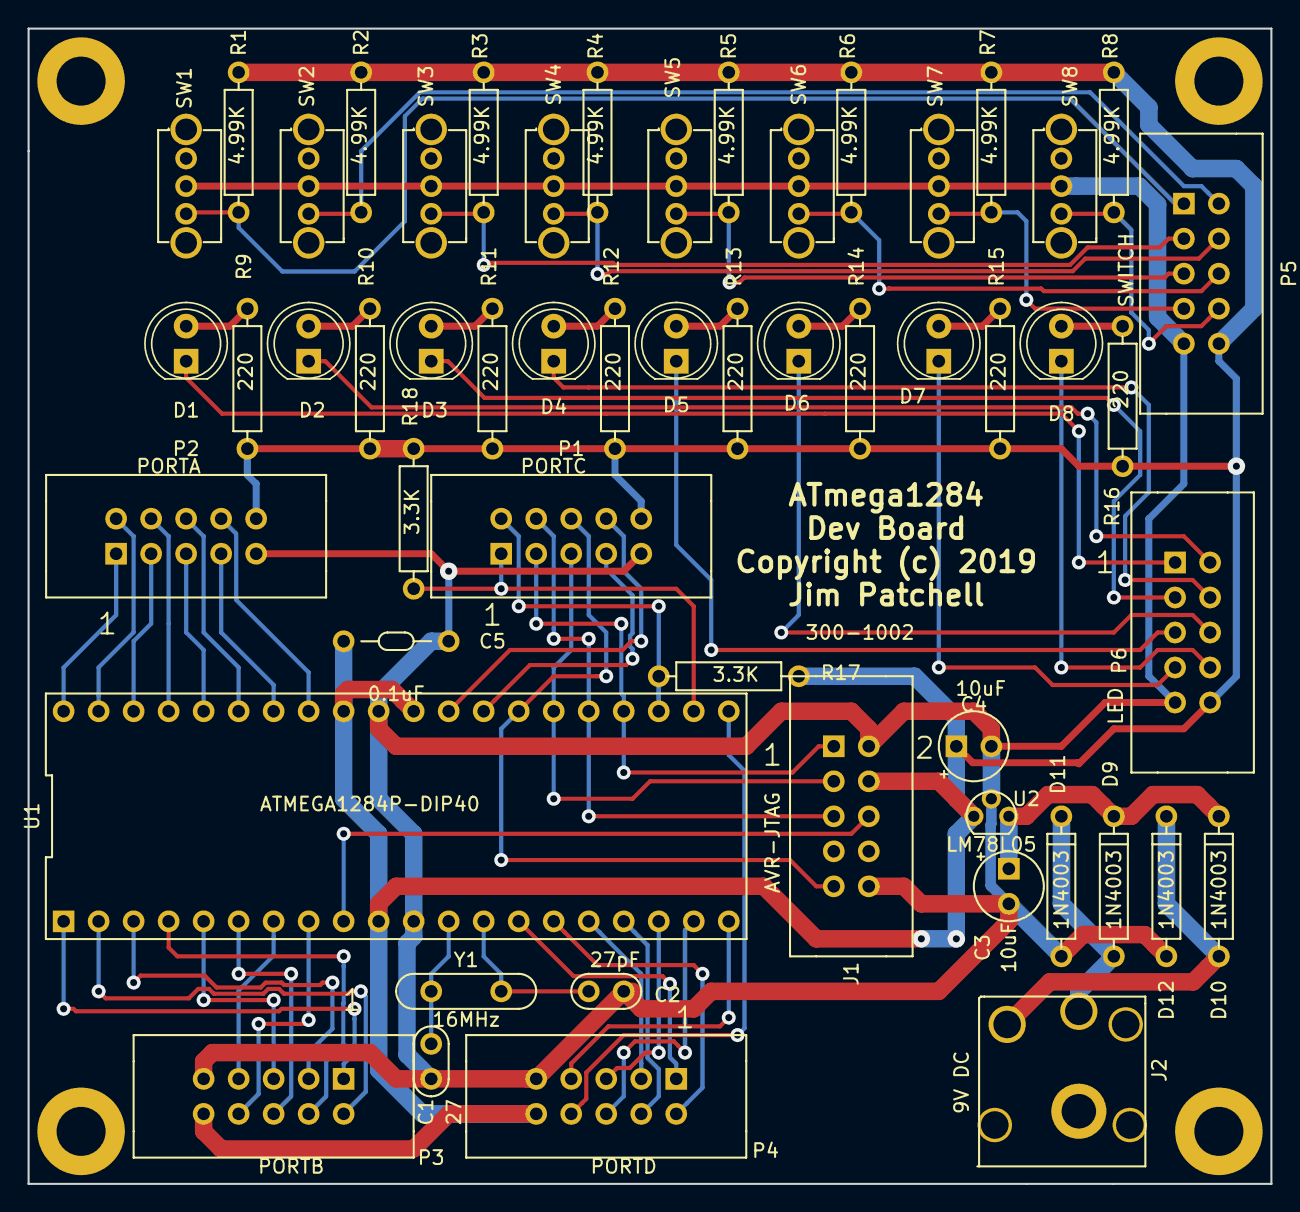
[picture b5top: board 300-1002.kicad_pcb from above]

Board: 2 copper layers, 90.2 x 83.8 mm, 58 parts (0 on the bottom side), 64 nets.

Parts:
C1: 27; CAP-0.1
C2: 27pF; CAP-0.1
C3, C4: 10uF; Cap-Pol-Rad-0.2_0.1
C5: 0.1uF; CAP-Bypass-0_3
D1, D2, D3, D4, D5, D6, D7, D8: LED; LED_5.0mm
D9, D10, D11, D12: 1N4003; DIODE0.4
J1: AVR-JTAG; IDC5x2_Vert
J2: 9V DC; DC-JACK-CUI-PJ-085AH
P1: PORTC; IDC5x2_Vert
P2: PORTA; IDC5x2_Vert
P3: PORTB; IDC5x2_Vert
P4: PORTD; IDC5x2_Vert
P5: SWITCH; IDC5x2_Vert
P6: LED; IDC5x2_Vert
P7, P8, P9, P10: PAD; MountingHole_140
R1, R2, R3, R4, R5, R6, R7, R8: 4.99K; AXIAL0_4
R9, R10, R11, R12, R13, R14, R15, R16: 220; AXIAL0_4
R17, R18: 3.3K; AXIAL0_4
SW1, SW2, SW3, SW4, SW5, SW6, SW7, SW8: SW-SPDT; SWITCH_SPDT-OS102011MS2QN1
U1: ATMEGA1284P-DIP40; DIP-40
U2: LM78L05; TO92
Y1: 16MHz; XTAL

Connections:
/A: D9.2, D11.1, J2.1
/B: D10.2, D12.1, J2.2
/VI: C3.1, D9.1, D10.1, U2.3
GND: C1.2, C2.2, C3.2, C4.2, C5.2, D11.2, D12.2, J1.2, J1.10, P1.9, P2.9, P3.9, P4.9, P5.9, P6.9, SW1.2, SW2.2, SW3.2, SW4.2, SW5.2, SW6.2, SW7.2, SW8.2, U1.11, U1.31, U2.2
unnamed: C1.1, U1.12, Y1.1
unnamed: C2.1, U1.13, Y1.2
unnamed: D1.1, P6.1
unnamed: D1.2, R9.1
unnamed: D2.1, P6.2
unnamed: D2.2, R10.1
unnamed: D3.1, P6.3
unnamed: D3.2, R11.1
unnamed: D4.1, P6.4
unnamed: D4.2, R12.1
unnamed: D5.1, P6.5
unnamed: D5.2, R13.1
unnamed: D6.1, P6.6
unnamed: D6.2, R14.1
unnamed: D7.1, P6.7
unnamed: D7.2, R15.1
unnamed: D8.1, P6.8
unnamed: D8.2, R16.1
unnamed: J1.1, P1.3, U1.24
unnamed: J1.3, P1.5, U1.26
unnamed: J1.5, P1.4, U1.25
unnamed: J1.6, U1.9
unnamed: J1.9, P1.6, U1.27
unnamed: P1.1, R18.2, U1.22
unnamed: P1.2, R17.2, U1.23
unnamed: P1.7, U1.28
unnamed: P1.8, U1.29
unnamed: P2.1, U1.40
unnamed: P2.2, U1.39
unnamed: P2.3, U1.38
unnamed: P2.4, U1.37
unnamed: P2.5, U1.36
unnamed: P2.6, U1.35
unnamed: P2.7, U1.34
unnamed: P2.8, U1.33
unnamed: P3.1, U1.1
unnamed: P3.2, U1.2
unnamed: P3.3, U1.3
unnamed: P3.4, U1.4
unnamed: P3.5, U1.5
unnamed: P3.6, U1.6
unnamed: P3.7, U1.7
unnamed: P3.8, U1.8
unnamed: P4.1, U1.14
unnamed: P4.2, U1.15
unnamed: P4.3, U1.16
unnamed: P4.4, U1.17
unnamed: P4.5, U1.18
unnamed: P4.6, U1.19
unnamed: P4.7, U1.20
unnamed: P4.8, U1.21
unnamed: P5.1, R1.2, SW1.1
unnamed: P5.2, R2.2, SW2.1
unnamed: P5.3, R3.2, SW3.1
unnamed: P5.4, R4.2, SW4.1
unnamed: P5.5, R5.2, SW5.1
unnamed: P5.6, R6.2, SW6.1
unnamed: P5.7, R7.2, SW7.1
unnamed: P5.8, R8.2, SW8.1
VCC: C4.1, C5.1, J1.4, P1.10, P2.10, P3.10, P4.10, P5.10, P6.10, R1.1, R2.1, R3.1, R4.1, R5.1, R6.1, R7.1, R8.1, R9.2, R10.2, R11.2, R12.2, R13.2, R14.2, R15.2, R16.2, R17.1, R18.1, U1.10, U1.30, U1.32, U2.1
